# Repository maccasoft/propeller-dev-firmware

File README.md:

## Propeller Development Board

This is my own version of a [Parallax Propeller](https://www.parallax.com) development board.

Uses a PIC microcontroller for the USB-Serial interface, can be powered from either USB or a dedicated power source, includes
an EEPROM to store the program and data, and provides a 2x20 pin header exposing all 32 I/O pins from the Propeller microcontroller,
power and control lines.

Compatible with all standard Propeller development tools.

**Parts List**

* R1 = 4.700 ohm 1/4 watt  
* R2 = 4.700 ohm 1/4 watt  
* R3 = 220 ohm 1/4 watt  
* R4 = 220 ohm 1/4 watt  
* R5 = 220 ohm 1/4 watt  
* R6 = 33.000 ohm 1/4 watt  
* C1 = 100.000 pF poli  
* C2 = 100.000 pF poli  
* C3 = 100.000 pF poli  
* C4 = 10 uF 63v elettr.  
* C5 = 10 uF 63v elettr.  
* C6 = 100.000 pF poli  
* C7 = 27 pF disc  
* C8 = 27 pF disc  
* C9 = 10.000 pF poli  
* DL1 = Red LED  
* DL2 = Yellow LED  
* DL3 = Green LED  
* XTAL1 = 5 MHz crystal  
* XTAL2 = 12 MHz crystal  
* IC1 = P8X32A  
* IC2 = 24LC512  
* IC3 = PIC18F14K50  
* IC4 = LM1117T-3.3  
* TR1 = Transistor NPN BC547  
* CN1 = USB-B connector  
* CN2 = 2.1mm DC power connector  
* CN3 = 2x20 pin header  
* JP1 = 1x3 pin header  
* P1 =  Button  

**JP1**

Power source selection:

```
+-+  
|1| USB  
|2| VIN  
|3| EXT  
+-+  
```

short pins 1-2 to power from USB  
short pins 2-3 to power from external source.

**CN3**

From top, P0/P1 are near the PIC/USB microcontroller.

```
+-------+-------+  
|     P0|P1     |  
|     P2|P3     |  
|     P4|P5     |  
|     P6|P7     |  
|     P8|P9     |  
|    P10|P11    |  
|    P12|P13    |  
|    P14|P15    |  
|    P16|P17    |  
|    P18|P19    |  
|    P20|P21    |  
|    P22|P23    |  
|    P24|P25    |  
|    P26|P27    |  
|SDA/P29|N.C.   |  
|SCL/P28|XI     |  
| TX/P30|RTS    |  
| RX/P31|CTS    |  
|  RESET|+3.3v  |  
|    GND|VIN    |  
+-------+-------+  
```

PCBs are shared on [OSH Park](https://oshpark.com) and can be ordered from there:
[https://oshpark.com/shared_projects/KALqBSpm](https://oshpark.com/shared_projects/KALqBSpm)

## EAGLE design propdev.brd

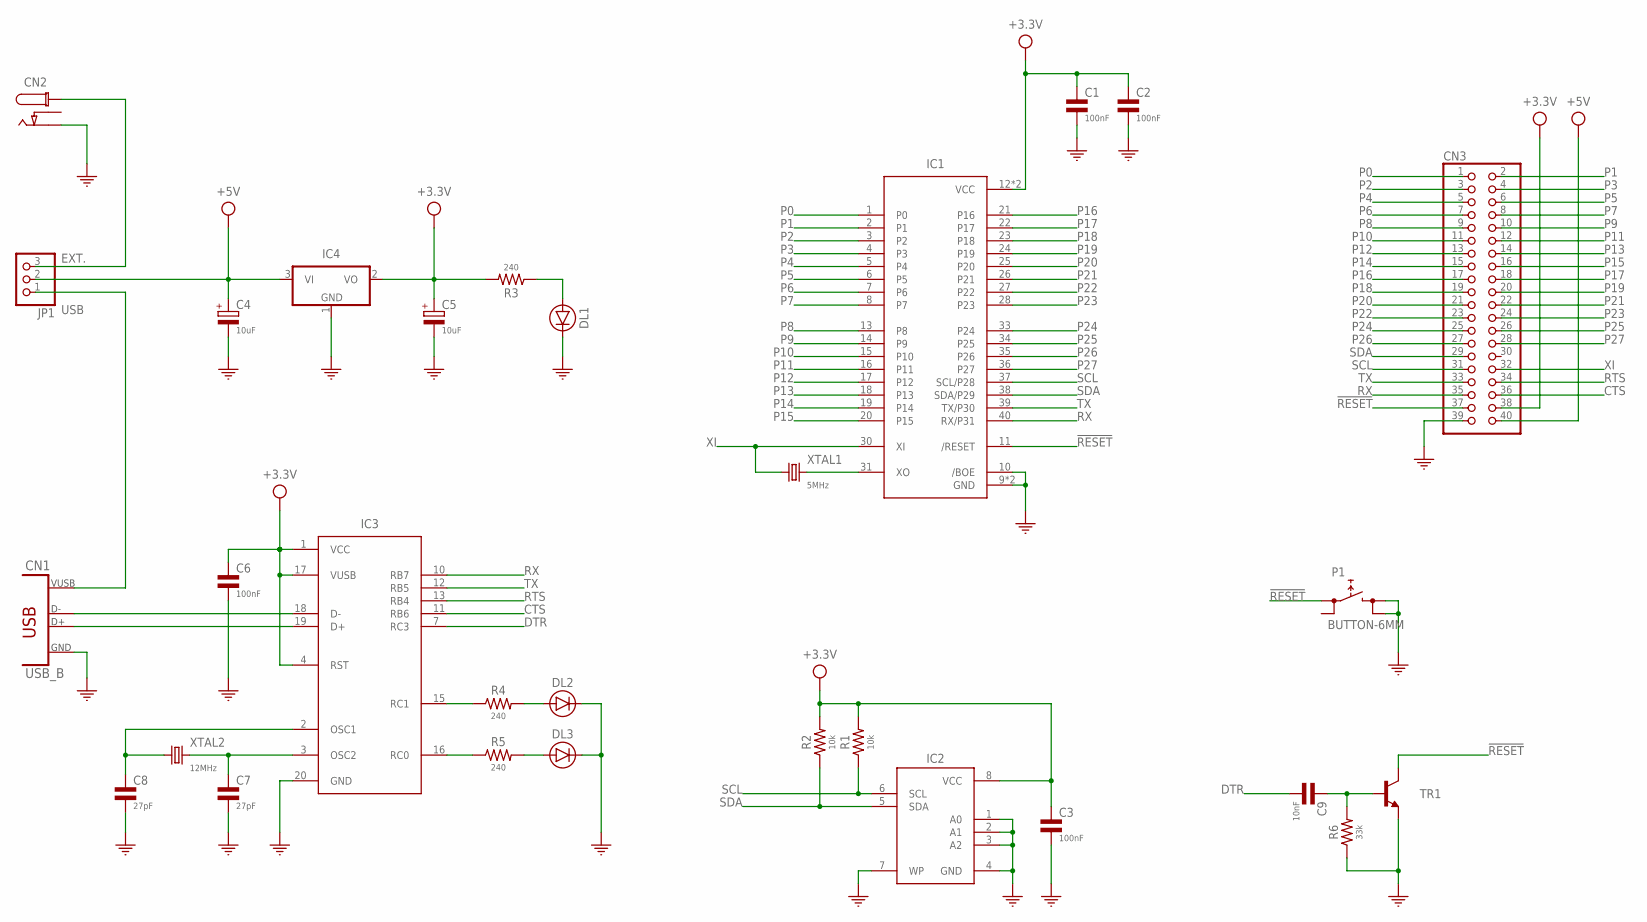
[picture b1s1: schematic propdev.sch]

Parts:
C1, C2, C3, C6: 100nF; C050-025X075
C4, C5: 10uF; E2,5-6
C7, C8: 27pF; C050-025X075
C9: 10nF; C050-025X075
CN1: USB_B; USB-B
CN2: DC_JACK; PJ-102A
CN3: PINHD-2X20B; 2X20B
DL1, DL2, DL3: LED-3MM; LED3MM
IC1: P8X32A; DIL40
IC2: 24LC512-I/P; DIL08
IC3: PIC18F14K50-I/P; DIL20
IC4: LM1117T-3.3; TO220H
JP1: PINHD-1X3; 1X03
P1: BUTTON-6MM; TL1105
R1, R2: 10k; 0207/10
R3, R4, R5: 240; 0207/10
R6: 33k; 0207/10
TR1: BC547; TO92
XTAL1: 5MHz; HC49/S
XTAL2: 12MHz; HC49/S

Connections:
!RESET!: CN3.37, IC1.11 (/RESET), P1.1 (0), TR1.3 (C)
+3.3V: C1.1, C2.1, C3.1, C5.+, C6.1, CN3.38, IC1.12 (VCC), IC1.32 (VCC), IC2.8 (VCC), IC3.1 (VCC), IC3.4 (RST), IC3.17 (VUSB), IC4.2 (VO), R1.2, R2.2, R3.2
+5V: C4.+, CN3.40, IC4.3 (VI), JP1.2
CTS: CN3.36, IC3.11 (RB6)
DTR: C9.2, IC3.7 (RC3)
EXT.: CN2.P1, JP1.3
GND: C1.2, C2.2, C3.2, C4.-, C5.-, C6.2, C7.2, C8.2, CN1.4 (GND), CN2.P3 (P2), CN3.39, DL1.K (C), DL2.K (C), DL3.K (C), IC1.9 (GND), IC1.10 (/BOE), IC1.29 (GND), IC2.1 (A0), IC2.2 (A1), IC2.3 (A2), IC2.4 (GND), IC2.7 (WP), IC3.20 (GND), IC4.1 (GND), P1.2 (1), P1.4 (1), R6.1, TR1.1 (E)
unnamed: IC3.16 (RC0), R5.1
unnamed: CN1.2 (D-), IC3.18 (D-)
unnamed: CN1.3 (D+), IC3.19 (D+)
unnamed: C7.1, IC3.3 (OSC2), XTAL2.2
unnamed: C8.1, IC3.2 (OSC1), XTAL2.1
unnamed: C9.1, R6.2, TR1.2 (B)
unnamed: DL2.A, R4.2
unnamed: DL3.A, R5.2
unnamed: IC3.15 (RC1), R4.1
unnamed: DL1.A, R3.1
unnamed: IC1.31 (XO), XTAL1.2
P0: CN3.1, IC1.1 (P0)
P1: CN3.2, IC1.2 (P1)
P2: CN3.3, IC1.3 (P2)
P3: CN3.4, IC1.4 (P3)
P4: CN3.5, IC1.5 (P4)
P5: CN3.6, IC1.6 (P5)
P6: CN3.7, IC1.7 (P6)
P7: CN3.8, IC1.8 (P7)
P8: CN3.9, IC1.13 (P8)
P9: CN3.10, IC1.14 (P9)
P10: CN3.11, IC1.15 (P10)
P11: CN3.12, IC1.16 (P11)
P12: CN3.13, IC1.17 (P12)
P13: CN3.14, IC1.18 (P13)
P14: CN3.15, IC1.19 (P14)
P15: CN3.16, IC1.20 (P15)
P16: CN3.17, IC1.21 (P16)
P17: CN3.18, IC1.22 (P17)
P18: CN3.19, IC1.23 (P18)
P19: CN3.20, IC1.24 (P19)
P20: CN3.21, IC1.25 (P20)
P21: CN3.22, IC1.26 (P21)
P22: CN3.23, IC1.27 (P22)
P23: CN3.24, IC1.28 (P23)
P24: CN3.25, IC1.33 (P24)
P25: CN3.26, IC1.34 (P25)
P26: CN3.27, IC1.35 (P26)
P27: CN3.28, IC1.36 (P27)
RTS: CN3.34, IC3.13 (RB4)
RX: CN3.35, IC1.40 (RX/P31), IC3.10 (RB7)
SCL: CN3.31, IC1.37 (SCL/P28), IC2.6 (SCL), R1.1
SDA: CN3.29, IC1.38 (SDA/P29), IC2.5 (SDA), R2.1
TX: CN3.33, IC1.39 (TX/P30), IC3.12 (RB5)
USB: CN1.1 (VUSB), JP1.1
XI: CN3.32, IC1.30 (XI), XTAL1.1

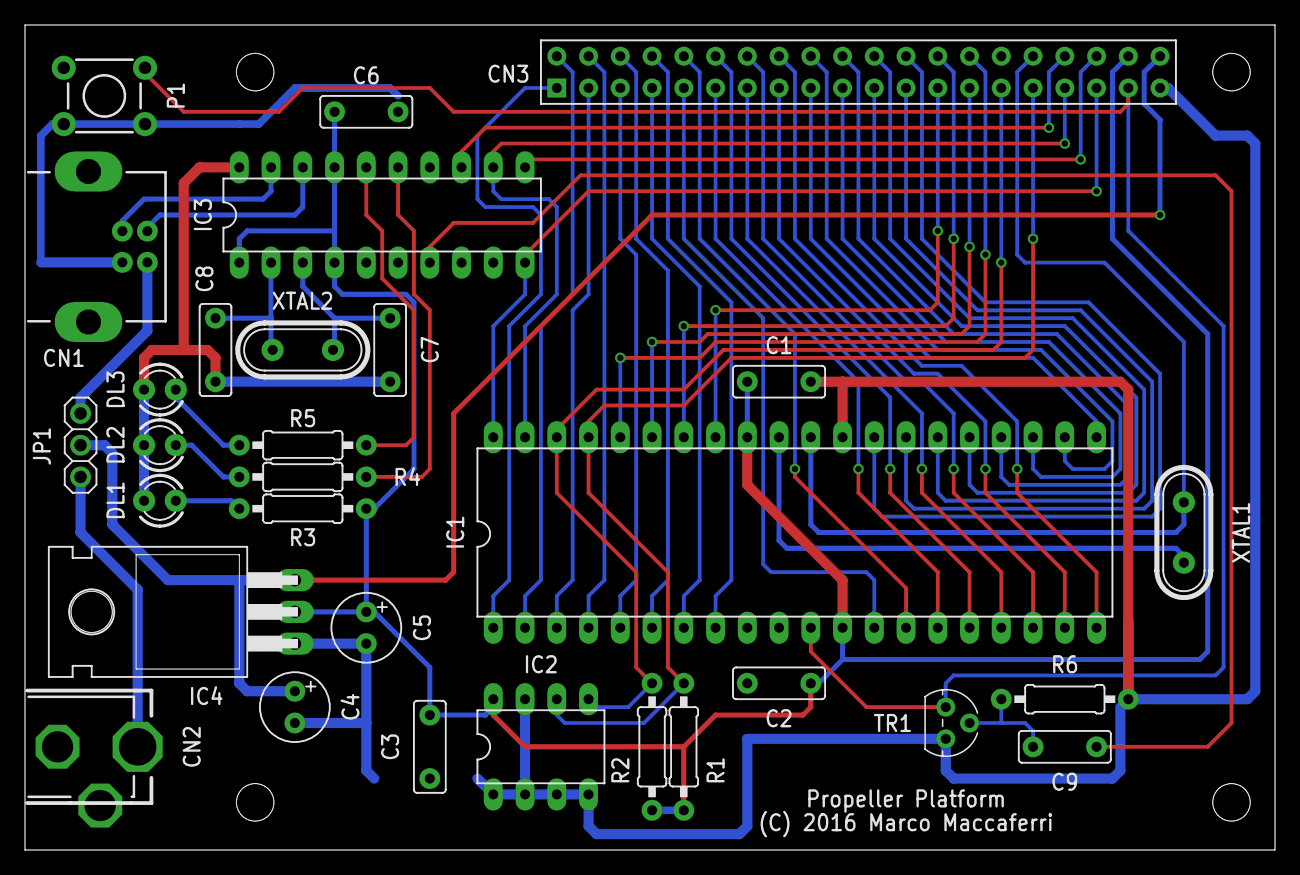
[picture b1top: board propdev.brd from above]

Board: 2 copper layers, 100.0 x 66.0 mm, 30 parts (0 on the bottom side), 53 nets.

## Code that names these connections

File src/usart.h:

/********************************************************************
 Software License Agreement:

 The software supplied herewith by Microchip Technology Incorporated
 (the "Company") for its PIC(R) Microcontroller is intended and
 supplied to you, the Company's customer, for use solely and
 exclusively on Microchip PIC Microcontroller products. The
 software is owned by the Company and/or its supplier, and is
 protected under applicable copyright laws. All rights are reserved.
 Any use in violation of the foregoing restrictions may subject the
 user to criminal sanctions under applicable laws, as well as to
 civil liability for the breach of the terms and conditions of this
 license.

 THIS SOFTWARE IS PROVIDED IN AN "AS IS" CONDITION. NO WARRANTIES,
 WHETHER EXPRESS, IMPLIED OR STATUTORY, INCLUDING, BUT NOT LIMITED
 TO, IMPLIED WARRANTIES OF MERCHANTABILITY AND FITNESS FOR A
 PARTICULAR PURPOSE APPLY TO THIS SOFTWARE. THE COMPANY SHALL NOT,
 IN ANY CIRCUMSTANCES, BE LIABLE FOR SPECIAL, INCIDENTAL OR
 CONSEQUENTIAL DAMAGES, FOR ANY REASON WHATSOEVER.
 *******************************************************************/

#ifndef USART_H
#define USART_H

#include <stdbool.h>

#define CLOCK_FREQ 48000000
#define GetSystemClock() CLOCK_FREQ

#define UART_ENABLE   RCSTAbits.SPEN

#define UART_TRISTx   TRISBbits.TRISB7
#define UART_TRISRx   TRISBbits.TRISB5
#define UART_Tx       PORTBbits.RB7
#define UART_Rx       PORTBbits.RB5

// Use following only for Hardware Flow Control
#define UART_DTS      PORTAbits.RA3
#define UART_DTR      LATCbits.LATC3
#define UART_RTS      LATBbits.LATB4
#define UART_CTS      PORTBbits.RB6

#define mEnableRxPU() {WPUB5 = 1;} // Enable Rx pin pull-up

#define mInitRTSPin() {TRISBbits.TRISB4 = 0;}   //Configure RTS as a digital output.
#define mInitCTSPin() {TRISBbits.TRISB6 = 1;}   //Configure CTS as a digital input.  (Make sure pin is digital if ANxx functions is present on the pin)
#define mInitDTSPin() {}//{TRISAbits.TRISA3 = 1;}   //Configure DTS as a digital input.  (Make sure pin is digital if ANxx functions is present on the pin)
#define mInitDTRPin() {TRISCbits.TRISC3 = 0;}   //Configure DTR as a digital output.




/*********************************************************************
* Function: void USART_Initialize(void);
*
* Overview: Initializes USART (RS-232 port)
*
* PreCondition: None
*
* Input: None
*
* Output: None
*
********************************************************************/
void USART_Initialize();

/******************************************************************************
 * Function:        void USART_putcUSART(char c)
 *
 * PreCondition:    None
 *
 * Input:           char c - character to print to the UART
 *
 * Output:          None
 *
 * Side Effects:    None
 *
 * Overview:        Print the input character to the UART
 *
 * Note:
 *
 *****************************************************************************/
void USART_putcUSART(char);

/******************************************************************************
 * Function:        void USART_mySetLineCodingHandler(void)
 *
 * PreCondition:    USB_CDC_SET_LINE_CODING_HANDLER mySetLineCodingHandler is defined
 *
 * Input:           None
 *
 * Output:          None
 *
 * Side Effects:    None
 *
 * Overview:        This function gets called when a SetLineCoding command
 *                  is sent on the bus.  This function will evaluate the request
 *                  and determine if the application should update the baudrate
 *                  or not.
 *
 * Note:
 *
 *****************************************************************************/
void USART_mySetLineCodingHandler(void);

/******************************************************************************
 * Function:        unsigned char USART_getcUSART()
 *
 * PreCondition:    None
 *
 * Input:           None
 *
 * Output:          unsigned char c - character to received on the UART
 *
 * Side Effects:    None
 *
 * Overview:        Get the input character from the UART
 *
 * Note:
 *
 *****************************************************************************/
unsigned char USART_getcUSART(void);

#endif //USART_H

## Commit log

2016-08-05 Enabled internal pull-up on serial rx pin

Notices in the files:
propdev.brd:
(C) 2016 Marco Maccaferri
